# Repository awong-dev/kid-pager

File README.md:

# Low-powered Kid Pager

## What is this and why does it exist?
Using expensive smart watches with also expensive cellular plans just so kids
can message their parents is ridiculous. The idea is to get something that
can run for a few dollars a month, be rugged in a backpack, and not require
constant changing.

Enter the Kid Pager.

This project builds a simple, customizable, location enabled, pager-style
device and accompanying Relay Server that can be fitted with an
ultra-cheapo SIM card to provide a mobile communication and location
system for coordinating with a child.

The Relay Server is designed to run on free-tier cloud services or on a
home server.  The complexity of the server is a bit above running a
Plex server.

The hardware is designed to be buildable by DIY hobbyists who know how
to do basic soldering.

Using the current bill of materials and the provided Relay Server, the
current prototype fits inside an Altoids Tin and has the following basic
features:
   * $2-$3/month for a soracom global coverage sim that talks to custom
     Chat server.
   * 2 week battery life per charge for basic usage
   * 2.9" e-ink screen so there NO blue light
   * _sluggish_ UI response (think kindle) to increase threshold for usage
   * GPS/GNSS and cell-tower location
   * full QWERTY keyboard
   * Temperature monitor cause everyone needs hour read of their kid's
     backpack temperature.

Because it is text only, the data usage is tiny so the data-only Soracom
sim never goes much above the base rate of $2.

We've been using this our family for about 2 months now with the thing being
beaten around inside a kid's backpack.

## Basic functionality and how it works

### Kidpager Relay Server + Native Chat
The system relies on a web-technology Relay Server for handling chat messages,
keeping location data, doing device management, pushing firmware updates, etc.
The Relay Server is the centrol point of control with all messages passing
through it so the parent can allow/deny/audit communications as makes
sense for their family.

It exports a web interface that can be used for sending/receiving chats
as well as for device management. This means your child can log into the
webpage at the home computer if they want instead of using the device
hardware allowing for access to a full keyboard when at home.

For the parent, the webpage is a "Progressive WebApp" and can be "installed"
on to your phone so that you can receive push notifications for new messages
from the native chat system.  This is actually not required for usage if
SMS or bridges into other chat systems are used (see later sections).

The Relay Server is is designed to run on the free tier of Google Firebase.
There is also a docker version so you can have complete control of the data.

### Talking to other families (Federation)

There is also federation support so that two families with different Relay
servers can register one-another to send messages back and forth.

It is also possible to host multiple families on one Relay Server. Which
one makes sense depends on data privacy considerations as to who may
access location + chat history for each family. In a multi-tenancy setup,
the admin has access to multiple families worth of data, but one admin
could host the setup for many people.

In a federated approach, only the authorized chat messages that cross the
boundries are forwarded but each family would have to run their own server.

### Extension #1: SMS
As a child gains more independence, being able to send messages to
others with SMS allows them the independence to extend their messaging
network.

Also, in emergency situations, it is frustrating to have a cellular
device, but not be able to reach someone even if you have their phone number.

Enabling SMS can be done by replacing the data-only Soracom sim with one
that supports SMS as well.

The SMS capabable SIM can be used two way:
  1. Installed directly on the device in place of the Soracom Sim.
  2. Installed in an android phone that you remote control (see Android Bridge section)

For (1), the SIM will also need a small data plan. For (2), it can be
an SMS only plan.

In either configuration, because it is a child device, all SMS
communication is controlled the Relay Server. Even in configuraiton
#1, though the device technically receives the SMS directly, the firmware
actually just passes it back up to the Relay Server so policies can be
applied. Only if it is deemed okay is it passed back to the child. This way
no random SPAM SMS messages can come through and the Relay Server always
maintains control over what the device can do.

### Extension #2: Android Bridge for SMS/WhatsApp/Google Chat/etc
This is a total hack that will likely be flaky but has worked
pretty well so far.

For this, you:
  1. Get an old android phone and leave it permanently plugged in
  at home.
  2. Install a SMS-only SIM card into that phone. (Now you have
  two SIM cards -- the $2/month Soracom in the Kid Pager device and
  a cheapo $5/month SMS-only one in the Android)
  3. Connect the phone to your wifi network to remove the need for data.
  4. Install whatever chat-apps you want and log them in.
  5. Side-load the custom Android Bridge app here that allows the Chat
  Server to remote control the Android phone.

The Android Bridge app works effectively as a remote-control for
the phone. When the pager wants to do an SMS or talk to WhatsApp
or Google chat, it sends a message to the Relay Server which then
directs the phone to forward it onwards. Incoming messages follow
that path in reverse.

Adding a new app can be done by direct Claude to vibe code an
interface.

Note that bridge does NOT give the pager device access to an entire
chat app (eg all WhatsApp contacts). Rather it subscribes to individual
conversations Relay Server. This is clunky but in a way better because
you have more fine grained control.

Why go through this complexity? Because ultimately, a custom closed
Relay Server, even with SMS, is too restrictive for the modern
communication envrionment.

However, any such bridge is fragile relying on hacks to watch
notifications, drive the UI via accessibility featuers, etc. It will likely
have bugs as time goes on.

## Hardware
The provided design uses an Altoids tin cause it looked cool. It's actually
not that great since it being metal which requires a much more expensive
external antenna that might be broken.

### Making it smaller.
The full QWERTY keyboard largest problem with shrinking the size
of the device.  After that, it's the antenna.  The battery can be
shrunk to whatever you want with a tradeoff of time-between charges.
(With a 2500 mAh battery, the system lasts about 2 weeks a charge)

So the first thing to play with is using a T-9 input system, a plastic
case so you can use a flex antenna on the inside of the case, and then
a smaller screen. You could probaby get close to an old Nokia style
candybar phone.

This would also have the benefit of possibly shaving up to $20/device off
the hardware cost as the external antennas are that much more expensive
that the internal ones.

## Privacy and Parental controls.

### Who can contact your kid + see their location
The Relay Server was designed with permission model close to a network firewall.

For each contact you can decide if

  1. Pager can send to contact
  2. Pager can receive from contact
  3. Contact may view or request location of Pager

For new and unknown contacts you can also set a policy to default allow or deny
any of the above.

A sensible configuraiton, for example, could be:
  1. Allow all send/receive from entries in a parent controlled Address Book
  2. For unknown contacts on SMS, allow if pager initiates, but log and notify the parent. This allows a kid to help a friend talk to the friend's parent.
  3. Disallow all inbound SMS to the pager number from an unknown contact, but log and notify parent. Prevents spam and also some protection against cyberbullying/harassment.

Of you could lock it down so that no one can communicate at all without the parent creating an explicit allow list,

## FAQ

### What happens with pictures and videos?

This thing is text only. The chat server will send a note that an [image] pr [video] was sent but that's it.

### What about other langauges?
The pager is built around unicode and is i18n ready! I even asked Claude to leave some hooks for an
IME (which could also be used for T-9 and predictive typing).  The problem with languages is fonts
and how much space to use in the font.  Currently, I have it doing a large chunk of Chinese and some
emojis. But you can swap that out.  The font is stored in a different partition from the code
and can be updated from the web.

### How do you update the firmware?
The Relay Server is able to push updates down for an Over The Air update (OTA) using the ESP32's OTA
infrastructure.  This allows pushing fonts also.  Firmware pushes use delta encoding making them
often around 50kb to 70kb in size which works prefectly fine in a 100Mb/month data plan.

### How does the protocol work?

In a nutshell, a provisioend Pager device maintains a connection to an MQTT
broker which provides a bidirectional channel to and from the Relay Server's
REST APIs. Provisining bind a pager to a broker and provides certs to
authenticate, sign, and/or encrypt messages as needed.

This channel is used to sent chat messages, location, and status updates. Data
is encoded in signed CBOR blob.

MQTT is used instead a direct TCP connection because it allows the Pager moden
to make heavy use of of eDRX power saving mode on LTE-M where it can sleep
while still staying on the network.

On a non-Soracomm sim, this connection is done with MQTTS using the provisioned
certs. This ensures an encrypted transmission across the open internet back to
the Relay Server, but incurs a fairly high TLS overhead for sending really short
messages.

With a Soracom SIM, Soracom Beam is used to avoid this. Instead of doing TLS
ourselves, plain MQTT is used to the Soracom Beam server. For this first hop,
we rely on the LTE layer to provide encryption which vastly reduces data usage
from the Pager on the cell plan. Soracom's Beam's proxy then creates a MQTTS
connection to our broker for transiting the open internet. Soracom's security
model guarnatees a secure network between the LTE termination and their
Beam endpoint so the threat model basically reduces to nation state that has
broken into a teleco system. That point which seems a good trade for saving
a lot of encryption handshake overhead (data usage + battery usage).

The Relay Server itself is just standard web techs (https, etc).

### How does location tracking work?

Location is derived from both cell-tower triangulation as well taking an
optional GNSS (superset of GPS) "fix" on the current location and broadcast
to the server.  The frequency of updates depends on whether the device is
in motion.  The device has an accelerometer which, when activated, causes
a faster location send. Otherwise, if it's just sitting in a backpack
for an hour, energy isn't wasted on updating location.

By nature of being on a cellular network, this is always some location
data avaliable for free just by nature of talking to a cellular antenna.
Within this part of Seattle, the precisions is frequently as good as
GNSS while also working inside buildings (that have cell signal) and
also being many times more power efficient.

However, if wanted, a GNSS antenna can be fitted on the device so it
can do a real GPS fix when there is line-of-sight to the sky.

### Can location be requested?

Yup. The Relay Server can send a signal down to tell the firmware that
location has been requested.

### Can I introduce filters on messages?

This thing is fairly simple web app that was almost entirely built with Claude
so by default there's no such functionality.

But because it is so simple, if you wanted to modify it so that messages
pass through some filter to do someething (eg, search for the word "applejack"
so that you can send an emergency broadcast to the City Spies), it'd be
very easy.

Or if you want to get super fancy, you could imagine sending everything into
an LLM that tries to do some sort of advanced cyberbullying detection...or
even process a code-switched multi-lingual chat to always provide some
sort of base translation.

Honestly, the sky's the limit.

But, personally, I think the expected use case is meant for "r u here yet?"
messages where the response is stuff like "almost. 5m."

## Technical details

### Repository layout

| Path | What it is |
|---|---|
| `docs/` | Design documents. Start at `docs/README.md`. `PROTOCOL.md` is the authoritative wire contract that code conforms to. |
| `firmware/` | ESP-IDF firmware for the Walter (ESP32-S3 + Sequans GM02SP) device. See `firmware/README.md` for build and bench steps. |
| `relay/` | FastAPI relay: webhook ingest, routing, delivery backends, admin and conversation APIs, device provisioning, authentication, retention. See `relay/README.md` to run it locally. |
| `web/` | Next.js + MUI web app on Firebase (Auth, Firestore listeners, FCM). See `web/README.md`. |
| `bridge-android/` | Android app that relays a member's SMS, voice and chat conversations to the relay (the bridge phone). |
| `home/` | Docker Compose stack for running the whole service on one machine you own. `setup.sh` writes its configuration. See `home/README.md`. |
| `hardware/` | Carrier board and enclosure design files. |
| `infra/` | Terraform for GCP (Cloud Run, Firestore, Firebase Hosting and Auth, Scheduler, Tasks, Secret Manager, Workload Identity Federation). See `infra/README.md`. |
| `tools/` | `pager_client.py` (simulated device and server driver), `e2e_v2.py` (end-to-end suite against the local stack), `send.py`, `provision.py`, `emqx_setup.py`. |
| `.github/workflows/` | `ci.yml` runs the relay unit tests and the end-to-end suite on push. `deploy.yml` builds the relay image and applies Terraform on a push to `main`. |

## Running your own server

The whole service runs on one machine you own, such as a Raspberry Pi, a NAS or a mini PC, with
Docker. You need a name that points at your home (a dynamic-DNS name is fine), a router that can
forward ports to that machine, and a reverse proxy (nginx or traefik) that already serves https
for that name.

```bash
cd home
./setup.sh               # asks for your server's name, writes the configuration, prints what to add to your proxy
docker compose up -d     # builds and starts the relay and the broker
```

`setup.sh` prints the nginx or traefik configuration, the ports to forward on your router and the
address to open to create the first admin. [`home/README.md`](home/README.md) is the full runbook:
ports, certificates, running without a proxy of your own, backups, automatic security updates and
Soracom Beam.

## Running a development stack

This is for working on the code, not for real use. Run the local stack (broker, Firebase emulators
and relay) and the end-to-end suite:

```bash
# Start the local stack (EMQX, Firebase emulators, relay)
cd relay
docker compose up -d --build
cd ..
python3 tools/emqx_setup.py
```

```bash
# [optional] Run all test scenarios, in text and CBOR wire encodings
relay/.venv/bin/python tools/e2e_v2.py
relay/.venv/bin/python tools/e2e_v2.py --wire cbor

# Or run individual scenarios
relay/.venv/bin/python tools/e2e_v2.py bootstrap setup_code address_book
```

Scenarios: `bootstrap`, `text_roundtrip`, `allowlist`, `republish`, `location_periodic`,
`location_on_demand`, `retention`, `bytes`, `address_book`, `setup_code`, `sms_log`, `bridge`,
`bridge_voice`, `bridge_whatsapp`, `receipts`, `bridge_health`. The implementation is in
`tools/e2e_v2.py`.

Unit tests and manual checklists are documented in `relay/README.md`, `web/README.md` and
`firmware/README.md`.

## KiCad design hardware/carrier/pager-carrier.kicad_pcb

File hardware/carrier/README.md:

# pager-carrier and pager-panel

KiCad 10 projects for the carrier board that replaces the Adafruit breakouts
around the Walter module, and for the small panel board that drives the
2.9" SSD1680 e-ink glass. The panel board sits between the glass and the
battery and is cabled to the carrier over a JST SH cable.

**Carrier: hand-edited.** The carrier `.kicad_sch` files are the source of
truth; `gen/carrier.py` / `gen/carrier_pcb.py` / `gen/build.py` describe an
earlier generated revision and must NOT be re-run (they overwrite the hand
edits). The sections below describe that generated revision; reference
designators and some parts differ in the hand-edited schematic.

**Panel: generated.** `gen/panel.py` + `gen/panel_pcb.py`; regenerate only the
panel with a driver that calls `build.build_panel(True)` (never `build.py`'s
main, which rebuilds the carrier too), then `panel_pcb.py --route` and
`finish_pcb.py panel` with KiCad's python.

## Layout of this directory

| Path | What |
|---|---|
| `pager-carrier.kicad_pro/.kicad_sch/.kicad_pcb` | carrier project, root schematic, board |
| `power.kicad_sch` … `peripherals.kicad_sch` | the five hierarchical sheets |
| `pager-carrier.kicad_sym`, `pager-carrier.pretty/` | project symbols (Walter, BQ25185, TPS62840, LIS2DW12, DRV2605L, MAX17048, rail power symbols) and custom footprints (Walter, BQ25185, TPS62840, USB4235, FH34SRJ 24S/6S) |
| `panel/` | pager-panel project (display ZIF, front-light ZIF, boost, 10-way SH), shares the symbol library above |
| `out/`, `panel/out/` | ERC and DRC reports, schematic PDF, BOM CSV, netlist, Freerouting DSN/SES |
| `gen/` | generator: `build.py` (schematics + exports), `carrier_pcb.py` / `panel_pcb.py` (boards, run with KiCad's python), `finish_pcb.py` |

The board scripts run under KiCad's python
(`/Applications/KiCad/KiCad.app/Contents/Frameworks/Python.framework/Versions/Current/bin/python3 gen/panel_pcb.py --route`).
`--route` needs a Freerouting jar: set `FREEROUTING_JAR`, or put it at
`gen/freerouting/freerouting-2.5.0.jar`.

## Custom footprints and where their numbers came from

- `Walter_Module_2x14_THT`: datasheet rev 1.1 (hw 1.6) section 6 plus the
  vendor `walter-solder.kicad_mod`. Rows 17.78 mm
  apart, 2.54 pitch, pin 1 at 9.72 mm from the USB-C end, 1.02 drill / 1.7 pad.
  The carrier sits above a header-side-up Walter, so the pattern is the
  **mirror** of the vendor's: pin 1 is on the +X row as seen from the carrier
  top. SIM holder, u.FL jacks and USB-C are marked on User.Comments.
- `BQ25185_WSON-10_DLH0010A_2.2x2mm_P0.4mm_EP0.9x1.5mm`: TI drawing 4226298/A
  (datasheet SLUSF65B): pads 0.5 x 0.2 on 0.4 pitch, columns 2.1 mm apart,
  thermal pad 0.9 x 1.5 with two 0.2 mm vias. Matches the SnapEDA footprint
  and KiCad's stock
  `Texas_DLH0010A_WSON-10-1EP_2.2x2mm_P0.4mm_EP0.9x1.5mm` pad for pad.
- `USB_C_Receptacle_GCT_USB4235_Vertical`: GCT drawing rev A.
  16 pads 0.30 x 0.87 on 0.5 pitch at x = ±0.25/0.75/1.25/2.75, rows at
  y = ±0.87; plated shell slots 0.6 x 0.85 (1.1 x 1.35 copper) at x = ±5.0; NPTH
  pegs 0.6 mm at x = ±3.75. Height 6.5 mm. Only ordering code: USB4235-03-C.
- `TPS62840_VSON-HR-8_DLC0008B_1.5x2mm_P0.5mm`: TI DLC0008B land pattern, pads
  0.6 x 0.25 at x = ±0.65 (the stock SOT-583-8 is 0.09 mm wider per side).
- `Hirose_FH34SRJ-24S-0.5SH` and `-6S-`: Hirose FH34SRJ catalog
  page 4 land pattern: contact pads 0.3 x 0.8 on 0.5 pitch, fitting pads
  0.4 x 0.8 at the E/F spans 3.3 mm behind the contacts; body D wide, 3.8 deep,
  **1.0 mm high**, top and bottom contact, back-flip actuator. Pin 1 at -X with
  the contacts (FPC entry) at -Y, the same convention as KiCad's FH12 footprints.
  KiCad 10 ships no FH34SRJ footprints.

## Mechanical placement (carrier, 85 x 52 mm, 1.0 mm FR4)

- Walter crosswise under the left 26 mm (its 55 mm axis runs across the 52 mm
  board width); header centre at (13.5, 24.73). USB-C end of the Walter at the
  top edge, antenna/SIM end at the bottom edge.
- Antenna notch 12 x 6 mm at the top-left edge (x 2.5–14.5): the u.FL jacks are
  at the Walter's **USB-C end**, not the antenna end.
  3 mm all-layer keep-outs around both jacks.
- Top strip (y 0–8): vertical USB-C J1, slide switch SW1, 10-way panel cable
  J3, battery J2 (cables exit toward the tin wall).
- Glass region (y 8–44.7, x 0.5–79.5): parts ≤ 2 mm only. Right end
  (x 62–79.5) left empty for the panel board.
- Bottom strip (y 44.7–52): keyboard J4 (cable up to the CardKB in the lid),
  LED J6 and haptic J7 (DNP), the 14 test pads (1.5 mm pitch), and the
  front-light button SW2 at the right end (80, 48.4), marked LIGHT.
- Walter region, top side only, between the header rows: CP2102N cluster,
  SN74LVC2G126 + UMH3N auto-reset, BQ25185 cluster, P-FET switch parts.
- Mounting holes H1–H4 at (17, 2.5), (82.8, 2.2), (82.8, 43.5), (2.5, 49.5).

## Part heights (low profile is critical; the CardKB lives in the lid)

| Part | Height above its board |
|---|---|
| J1 USB4235 vertical USB-C | 6.5 mm (the horizontal fallback is 3.2) |
| J2, J4 JST PH side-entry (S2B/S4B-PH-SM4-TB) | 5.5 mm (6.0 deep; JST ePH catalog p.4) |
| SW1 slide switch JS102011SAQN | 3.5 mm |
| J3 JST SH side-entry SM10B-SRSS-TB | 2.9 mm |
| SW2 tactile SKQGAFE010 | 1.5 mm (sits beside the glass, below the glass top) |
| everything under the glass | ≤ 1.3 mm: 0805 caps 1.25, SOT-23 1.1, QFN 0.9, L2 1.0 |
| glass GDEY029T94-FL03 | 2.01 mm incl. the front-light plate |
| panel board | 1.0 mm FR4 + 1.5 mm (L1) ; FH34SRJ ZIFs 1.0, SOD-123 1.1 — a 0.8 mm board is fine |

So above the carrier: glass stack ≈ 1.3 + 2.0 (or panel 1.0 + 1.5 + 2.0 at the
tail end), and the USB-C at 6.5 is the only thing taller than 3.5 mm.

## Design notes

1. **CP2102N package**: the GQFN20 has no DTR pin, so auto-reset is
   impossible with it. U5 is **CP2102N-A02-GQFN24** (DTR pin 23, RTS 19,
   VIO tied to VDD, RSTb pull-up 1 k per datasheet, VBUS sense via
   22.1 k / 47.5 k, 4.7 µF + 100 nF per supply pin).
2. **TPS62840DLCR is not a fixed 3.3 V part**: VSET takes a 267 k resistor to
   GND for 3.3 V; pin 8 is VOS (output sense), wired to 3V3.
3. **PWR_FLAG**: SYS is driven by the charger's SYS power-output pin, so a
   flag there is an ERC error and SYS has none; the other rails keep theirs.
4. **TPS22917 QOD** left open (open-collector to power-output is an ERC
   error); tie to VOUT in layout if quick discharge of the panel rail is wanted.
5. **Panel reference circuit** follows the GDEY029T94 spec sheet:
   RESE 2.2 Ω, L1 47 µH ≥ 0.43 A (cjiang
   FNR3015S470MT, 3 x 3 x 1.5 mm), 1 MΩ GDR pull-down, FPC pin 5 = VSH2 and
   pin 20 = VSH1 (both 1 µF/25 V), VPP open. Diode orientation: D2 anode on
   the pump node, D1 anode on VGL.
6. **ISET** is 604 Ω (600 Ω is not an E96 value): 497 mA. ILIM/VSET 18 k gives
   the 500 mA limit (475 mA typ) with 4.20 V; the DNP alternate is 13 k
   (1.1 A), not 1 A.
7. **TS/MR**: a single 10 k to GND, per the datasheet "TS not used" text.
8. **Front light = GDEY029T94-FL03**: the light has its own
   6-pin 0.5 mm flex (pins 1-2 anode, 3-4 NC, 5-6 cathode; 4 LEDs in parallel,
   Vf 2.75/2.8/3.3 V, 60 mA max; 3.5 mm wide, ~30 mm long, leaves the glass at
   the corner next to the display tail). Its ZIF (panel J3, FH34SRJ-6S) is on
   the panel board and the anode/cathode ride the panel cable (pins 9/10), so
   the cable is a 10-way SH. The ballast is 0 Ω and Q4 (AO3400A) carries a
   15 Ω source resistor with an MMBT3904 base-emitter across it, a ~45 mA
   clamp that is independent of SYS and of firmware; the 1 k gate resistor
   lets the BJT pull the gate down. Dim with FL_PWM. Fits both the FL03
   (60 mA max) and the Orient AEZ122250A00 light (3 LEDs, 45 mA at Vf 3.3 V).
8b. **Two front-light ZIF positions on the panel board.** The 6-pin
   light flex pinout (1-2 anode, 3-4 NC, 5-6 cathode) is the same on both
   panels, but where the tail leaves the glass is not. J3 "FL-A" (fitted)
   is for the FL03 tail; J4 "FL-B" (DNP) is for the Orient
   AEZ122250A00-2.13ENRWS tail. The Orient light's pin numbers run opposite
   to its display tail's, so J4 is wired 1-2 cathode / 5-6 anode. The cable's
   FL_P / FL_N reach FL_A / FL_K through two bridged solder jumpers JP1/JP2
   (1-2 bridged = straight; cut and bridge 2-3 = crossover), so a tail whose
   polarity turns out mirrored is a jumper change. The display ZIF J1 and its
   reference circuit (47 µH, 2.2 Ω, MBR0530, 1 µF/25 V, BS1 low) are
   identical in the Good Display and Orient sheets, so the same panel board
   takes either glass.
   From the drawings (GDEY029T94-FL03-CAD.pdf and AEZ122250A00-2.13ENRWS
   rev 1.0 p.5): both front-light tails leave on the **pin-24 side** of the
   display tail (front view). FL03: tail centre 15.5 mm from the display tail
   centre (display tail left edge 10.42 from the LGP edge + 0.80 LGP inset,
   12.50 wide; FL tail 3.50 wide, 2.00 from the glass corner), 11.5 mm long
   with the contacts at 9.5-11.5, so J3 sits in the edge row. Orient 2.13":
   10.8 mm, FL tail 20.0 mm long (contacts 17.8-20.0), display tail 14.3 mm;
   its FL pins run 6->1 away from the display tail. Both ZIFs therefore sit
   left of J1 on the board (J1 pad 24 is on the left): J3 at J1.x-15.5 in the
   edge row, J4 at J1.x-10.8 one row inboard, since 5.5 mm wide ZIFs 4.7 mm
   apart cannot share a row.
9. **Front-light button** SW2: FL_BTN on IO4 (header pin 15,
   RTC GPIO so it can be an ext1 wake), 100 k pull-up to 3V3, 100 nF, switch to
   GND. TP13 is on the same net.
10. **Fuel gauge** U10 is populated. CELL and VDD both on VBAT,
    QSTRT and CTG to GND, EP to GND.
11. **MAX17048 footprint**: stock `TDFN-8-1EP_2x2mm_P0.5mm_EP0.8x1.2mm`
    (matches the Maxim 21-0168 drawing); DRV2605L uses `TSSOP-10_3x3mm_P0.5mm`
    (TI DGS land within 0.05 mm).
12. **Walter mounting**: the datasheet has no header-side-up guidance; the
    nano-SIM then faces the carrier and loads from the antenna end, which is
    within ~1 mm of the tin wall. Fit the SIM before mounting.
13. **References**: Q2 is one UMH3N holding both auto-reset transistors; the
    carrier's 10-way display connector is J3; the panel board
    owns the display ZIF (J1), L1, Q5, D1–D3, R4, C3–C5, plus the
    front-light ZIF as J3.
14. **BOM**: SN74LVC2G126DCUR (VSSOP-8) and USB4235 are not stocked by
    LCSC/JLCPCB (hand-place; DCTR is MSOP-8 0.65 mm, a different footprint).
    The BOM carries LCSC numbers; basic parts preferred.
15. **Routing** is Freerouting's output (GND routed as tracks, then pours on
    both layers). The boost loop on the panel and the USB D+/D− pair deserve
    a manual look.

## Sleep-current audit

Battery only, SW1 on, Walter asleep. Carrier parts, from the datasheets:

| Consumer | Sleep current | Note |
|---|---|---|
| BQ25185 battery quiescent (IQ_BAT) | 4 µA typ, 5 max | unavoidable while the cell is connected |
| MAX17048 | 3 µA hibernate (23 µA active) | firmware must leave HIBRT at its default so it auto-hibernates, or force hibernate |
| TPS62840 3V3 buck | ~0.1 µA (36 nA VIN + 56 nA VOS) | |
| TPS22917 (3V3_EPD off) | 10 nA | 0.5 µA when on |
| LIS2DW12 low-power mode 1 | ~1 µA | shake wake; 50 nA if powered down |
| Q1 gate network | **1.9 µA** | 2.2 M pull-up (a 100 k would draw 38 µA); the ON switch pulls the gate low through 10 k + pull-up |
| SN74LVC2G126 U6 | **0** | VCC is BRG_VDD (CP2102N regulator), so it is unpowered without USB; Ioff outputs, ESP_RX0 held by its 10 k |
| CP2102N | 0 | bus powered |
| STAT/ACC/RX0/FL_BTN pull-ups, VBUS dividers | 0 | all idle high or on VBUS |
| front light, Q4, keyboard rail, panel rail | 0 | switched off |

Carrier total ≈ 10 µA on top of the Walter's own deep-sleep draw. The fuel
gauge is the biggest remaining item.

## TPS62840 fixed-voltage question

There is no fixed-3.3 V part. Every TPS6284x orderable (TPS62840 1.8–3.3 V,
TPS62841 0.8–1.55 V, TPS62842 1.8–3.6 V; DLC, YBG and DGR packages) sets its
output with the VSET resistor. The 267 k 0603 stays.

## Open questions

- Tin interior height with the lid closed versus 8.5 + 1 + 6.5 (USB4235) mm.
- GDEY029T94 tail pin-1 side after the 180° fold. The FH34SRJ has contacts
  on both faces, so the fold cannot leave the tail unconnected, but a wrong
  face mirrors the pin order (1↔24). The footprint uses the FH12
  bottom-contact convention; confirm on a physical panel
  before ordering. Same for the 6-pin front-light tail (a mirror there only
  swaps anode and cathode: no light, no damage; fix = change JP1/JP2 on the
  panel board).
- UC8151 / IL0373 panels (Good Display GDEW series, Waveshare non-V2) use a
  different RESE value; if those must fit, give R4 a second parallel 0603
  footprint and confirm the value from a specific sheet.
- Walter header geometry against a physical module before ordering.
- Battery lead polarity (Adafruit 328) versus J2 pin 1.
- LTE peak current at VIN, to confirm 100 µF + 10 µF and the
  P-FET drop at a 3.4 V cell.
- Where exactly the panel board sits relative to the glass tail (the carrier
  keeps x 62–79.5 under the glass clear for it).

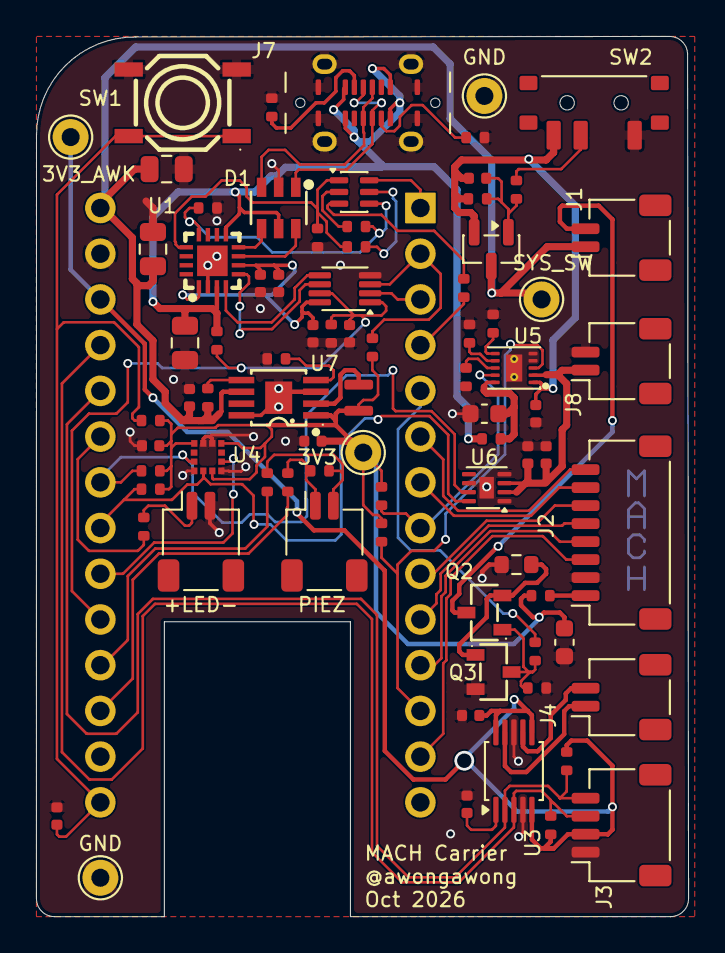
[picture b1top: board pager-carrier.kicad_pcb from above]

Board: 2 copper layers, 36.2 x 48.9 mm, 81 parts (0 on the bottom side), 63 nets.

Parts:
C1: 10uF; C_0805_2012Metric
C2, C4, C8, C11, C13, C16, C17: 100nF; C_0402_1005Metric_NoSilk
C3, C9, C10: 1uF; C_0402_1005Metric_NoSilk
C5, C6: 22uF; C_0805_2012Metric
C7: 10uF; C_0603_1608Metric
C12: 1uF; C_0603_1608Metric
C14, C15, C18, C19: 10uF; C_0402_1005Metric_NoSilk
D1: USBLC6-2SC6_C2687116; SOT-23-6_L2.9-W1.6-P0.95-LS2.8-BL
J1, J4, J5, J6, J8: Conn_01x02; JST_SH_SM02B-SRSS-TB_1x02-1MP_P1.00mm_Horizontal
J2: Conn_01x08; JST_SH_SM08B-SRSS-TB_1x08-1MP_P1.00mm_Horizontal
J3: Conn_01x04; JST_SH_SM04B-SRSS-TB_1x04-1MP_P1.00mm_Horizontal
J7: USB_C_Receptacle_USB2.0_16P; USB_C_Receptacle_ShouHan_TYPE-C-16PLT-H6.5_Vertical
L1: 2.2uH; L_Murata_DFE201610P_NoSilk
M1: Walter; Walter_Module_2x14_THT
Q1: UMH3N; SOT-363_SC-70-6
Q2: AO3400A; SOT-23-3_L2.9-W1.3-P1.90-LS2.4-BR
Q3: MMBT3904-C20526; SOT-23-3_L2.9-W1.3-P1.90-LS2.4-BR
Q4: AO3401A; SOT-23
R1, R2, R3, R9, R31, R32: 100k; R_0402_1005Metric_NoSilk
R4, R5, R11, R21, R23, R25, R27: 10k; R_0402_1005Metric_NoSilk
R6, R7, R20: 0R; R_0402_1005Metric_NoSilk
R8: 1k; R_0402_1005Metric_NoSilk
R10: 15R; R_0603_1608Metric
R12, R13, R14, R15, R26, R28: 4.7k; R_0402_1005Metric_NoSilk
R16, R17, R18: 220R; R_0402_1005Metric_NoSilk
R19, R29: 1M; R_0402_1005Metric_NoSilk
R22: 18k; R_0402_1005Metric_NoSilk
R24: 620R; R_0402_1005Metric_NoSilk
R30, R33: 51k; R_0402_1005Metric_NoSilk
SW1: TS-1187A-S16; SW-SMD_4P-L5.2-W5.2-P3.70-LS6.4
SW2: SW_SPDT; SW_SPDT_ShouHan_MSS12C02LS_TopActuated
TP1: 3V3; TestPoint_THTPad_D2.0mm_Drill1.0mm
TP2: SYS_SW; TestPoint_THTPad_D2.0mm_Drill1.0mm
TP3, TP5: GND; TestPoint_THTPad_D2.0mm_Drill1.0mm
TP4: 3V3_AWK; TestPoint_THTPad_D2.0mm_Drill1.0mm
U1: CH343P; TQFN-16_L3.0-W3.0-P0.50-BL-EP1.7
U2: 74LVC2G126; VSSOP-8_2.3x2mm_P0.5mm
U3: DRV2605LDGSR; TSSOP-10_3x3mm_P0.5mm
U4: LIS2DW12TR-MS; LGA-12_2x2mm_P0.5mm_NoSilk
U5: BQ25185DLHR; BQ25185_WSON-10_DLH0010A_2.2x2mm_P0.4mm_EP0.9x1.5mm
U6: MAX17048G+T10; TDFN-8-1EP_2x2mm_P0.5mm_EP0.8x1.2mm
U7: TPS62842DGRR; HVSSOP-8_L3.0-W3.0-P0.65-LS4.9-BL-EP

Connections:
3V3: C7.1, C11.1, C19.1, L1.2, R3.2, R7.1, R11.2, R14.1, R15.1, R23.1, R25.1, TP1.1 (1_1), U4.3 (VDDIO), U4.7 (VDD), U4.10 (CS), U7.1 (VOS)
3V3_AWK: C9.1, J3.2, M1.26 (3V3_OUT), R12.1, R13.1, TP4.1 (1_1), U3.5 (EN), U3.6 (VDD/NC), U3.10 (VDD)
/Core/3V3_J1: J2.1, R7.2
/Core/ACC_INT1: M1.20 (IO16), U4.5 (INT1)
/Core/AWK_EN_N: M1.4 (DFU/3V3_EN), R6.2
/Core/AWK_SCL: J3.4, M1.24 (IO9), R13.2, U3.2 (SCL)
/Core/AWK_SDA: J3.3, M1.25 (IO10), R12.2, U3.3 (SDA)
/Core/BRG_3V3: C2.2, C3.2, C8.1, U1.1 (VIO), U1.6 (V3), U2.8 (VCC)
/Core/BRG_RXD: U1.5 (RXD), U2.6
/Core/BRG_TXD: U1.4 (TXD), U2.5
/Core/EINK_BUSY: J2.8, M1.6 (IO11)
/Core/EINK_CS: J2.5, M1.10 (IO40)
/Core/EINK_DC: J2.6, M1.9 (IO39)
/Core/EINK_MOSI: J2.4, M1.11 (IO41)
/Core/EINK_RST: J2.7, M1.7 (IO13)
/Core/EINK_SCK: J2.3, M1.13 (IO2)
/Core/ESP_EN: M1.1 (RESET), Q1.6 (C1)
/Core/ESP_RX0: M1.2 (IO44/RX0), R11.1, U2.3
/Core/ESP_TX0: M1.3 (IO43/TX0), U2.2
/Core/EXT_LED: M1.23 (IO8), R18.1
/Core/FL_BTN: C4.1, M1.15 (IO4), R3.1, SW1.1, SW1.2
/Core/FL_N: J1.2, Q2.3 (D)
/Core/FL_PWM: M1.5 (IO12), R8.1
/Core/PIEZ_N: M1.18 (IO7), R17.1
/Core/PIEZ_P: M1.17 (IO6), R16.1
/Power/SW: L1.1, U7.2 (SW)
/Power/SYS: C13.2, C14.1, Q4.2 (S), R29.2, SW2.3 (C), U5.1 (SYS)
/Power/SYS_GATE: C13.1, Q4.1 (G), R27.2, R29.1
/Power/VBAT: C15.1, C16.1, J8.1, U5.2 (BAT), U6.2 (CELL), U6.3 (VDD)
/Power/VSET: R33.1, U7.4 (VSET)
AON_SCL: M1.22 (IO18), R15.2, U4.12 (SCL), U6.7 (SCL)
AON_SDA: M1.21 (IO17), R14.2, U4.2 (SDA), U6.8 (SDA)
CHG_STAT1: M1.8 (IO38), R23.2, U5.9 (STAT1)
CHG_STAT2: M1.12 (IO42), R25.2, U5.3 (STAT2)
GND: C1.2, C2.1, C3.1, C4.2, C5.2, C6.2, C7.2, C8.2, C9.2, C10.2, C11.2, C12.2, C14.2, C15.2, C16.2, C17.2, C18.2, C19.2, D1.2 (GND), J2.2, J3.1, J5.2, J7.A1 (GND), J7.A12 (GND), J7.B1 (GND), J7.B12 (GND), J7.SH (SHIELD), J8.2, M1.27 (GND), Q3.2 (E), R1.2, R2.2, R9.2, R10.2, R21.2, R22.2, R24.2, R26.2, R28.2, R31.2, R33.2, SW1.3, SW1.4, SW2.1 (A), TP3.1 (1_1), TP5.1 (1_1), U1.2 (GND), U1.17 (EP), U2.4 (GND), U3.4 (IN/TRIG), U3.8 (GND), U4.1 (SDO/SA0), U4.4 (NC(GND)), U4.8 (GNDIO), U4.9 (GND), U5.4 (~CE), U5.5 (GND), U5.11 (EP), U6.1 (CTG), U6.4 (GND), U6.6 (QSTRT), U6.9 (EP), U7.3 (MODE), U7.8 (GND), U7.9 (EP)
unnamed: D1.1 (I/O1), J7.A6 (D+), J7.B6 (D+)
unnamed: D1.3 (I/O2), J7.A7 (D-), J7.B7 (D-)
unnamed: J4.1, U3.9 (OUT-)
unnamed: J4.2, U3.7 (OUT+)
unnamed: J5.1, R18.2
unnamed: J6.1, R16.2, R19.2
unnamed: J6.2, R17.2, R19.1
unnamed: J7.A5 (CC1), R28.1
unnamed: J7.B5 (CC2), R26.1
unnamed: Q1.2 (B1), R4.2
unnamed: Q1.1 (E1), R2.1, R5.1, U1.13 (RTS)
unnamed: Q1.5 (B2), R5.2
unnamed: Q1.3 (C2), R6.1
unnamed: Q1.4 (E2), R1.1, R4.1, U1.12 (DTRTNOW)
unnamed: Q2.1 (G), Q3.3 (C), R8.2, R9.1
unnamed: Q2.2 (S), Q3.1 (B), R10.1
unnamed: R27.1, SW2.2 (B)
unnamed: C10.1, U3.1 (REG)
unnamed: R22.1, U5.7 (ILIM/VSET)
unnamed: C12.1, R20.2, U5.10 (IN)
unnamed: R24.1, U5.8 (ISET)
unnamed: R21.1, U5.6 (TS/MR)
unnamed: R32.2, U7.5 (EN)
SYS_SW: C5.1, C6.1, C18.1, J1.1, M1.28 (VIN), Q4.3 (D), R32.1, TP2.1 (1_1), U7.6 (VIN)
USB_DM: D1.4 (I/O2), U1.8 (UD-)
USB_DP: D1.6 (I/O1), U1.7 (UD+)
VBUS: C1.1, D1.5 (VBUS), J7.A4 (VBUS), J7.A9 (VBUS), J7.B4 (VBUS), J7.B9 (VBUS), R20.1, R30.1, U1.3 (VDD5), U1.9 (VBUS)
VBUS_DET: C17.1, M1.19 (IO15), R30.2, R31.1, U2.1, U2.7

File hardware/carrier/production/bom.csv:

Designator,Footprint,Quantity,Value,LCSC Part #
C1,0805,1,10uF,C15850
"C10, C3, C9",0402,3,1uF,C52923
"C11, C13, C16, C17, C2, C4, C8",0402,7,100nF,C1525
C12,0603,1,1uF,C15849
"C14, C15, C18, C19",0402,4,10uF,C15525
"C5, C6",0805,2,22uF,C45783
C7,0603,1,10uF,C19702
D1,SOT-23-6_L2.9-W1.6-P0.95-LS2.8-BL,1,USBLC6-2SC6_C2687116,C2687116
"J1, J4, J5, J6, J8",JST_SH_SM02B-SRSS-TB_1x02-1MP_P1.00mm_Horizontal,5,Conn_01x02,C160402
J2,JST_SH_SM08B-SRSS-TB_1x08-1MP_P1.00mm_Horizontal,1,Conn_01x08,C160407
J3,JST_SH_SM04B-SRSS-TB_1x04-1MP_P1.00mm_Horizontal,1,Conn_01x04,C160404
J7,USB_C_Receptacle_ShouHan_TYPE-C-16PLT-H6.5_Vertical,1,USB_C_Receptacle_USB2.0_16P,C3151748
L1,L_Murata_DFE201610P_NoSilk,1,2.2uH,C5832344
M1,Walter_Module_2x14_THT,1,Walter,Walter (DPTechnics)
Q1,SOT-363_SC-70-6,1,UMH3N,C62892
Q2,SOT-23-3_L2.9-W1.3-P1.90-LS2.4-BR,1,AO3400A,C20917
Q3,SOT-23-3_L2.9-W1.3-P1.90-LS2.4-BR,1,MMBT3904-C20526,C20526
Q4,SOT-23,1,AO3401A,C15127
"R1, R2, R3, R31, R32, R9",0402,6,100k,C25741
R10,0603,1,15R,C22810
"R11, R21, R23, R25, R27, R4, R5",0402,7,10k,C25744
"R12, R13, R14, R15, R26, R28",0402,6,4.7k,C25900
"R16, R17, R18",0402,3,220R,C25091
"R19, R29",0402,2,1M,C26083
"R20, R6, R7",0402,3,0R,C17168
R22,0402,1,18k,C25762
R24,0402,1,620R,C4961
"R30, R33",0402,2,51k,C25794
R8,0402,1,1k,C11702
SW1,SW-SMD_4P-L5.2-W5.2-P3.70-LS6.4,1,TS-1187A-S16,C42420254
SW2,SW_SPDT_ShouHan_MSS12C02LS_TopActuated,1,SW_SPDT,C3008584
U1,TQFN-16_L3.0-W3.0-P0.50-BL-EP1.7,1,CH343P,C2846043
U2,VSSOP-8_2.3x2mm_P0.5mm,1,74LVC2G126,C2652104
U3,TSSOP-10_3x3mm_P0.5mm,1,DRV2605LDGSR,C527464
U4,LGA-12_2x2mm_P0.5mm_NoSilk,1,LIS2DW12TR-MS,C50385411
U5,BQ25185_WSON-10_DLH0010A_2.2x2mm_P0.4mm_EP0.9x1.5mm,1,BQ25185DLHR,C19725033
U6,TDFN-8-1EP_2x2mm_P0.5mm_EP0.8x1.2mm,1,MAX17048G+T10,C2682616
U7,HVSSOP-8_L3.0-W3.0-P0.65-LS4.9-BL-EP,1,TPS62842DGRR,C2873354

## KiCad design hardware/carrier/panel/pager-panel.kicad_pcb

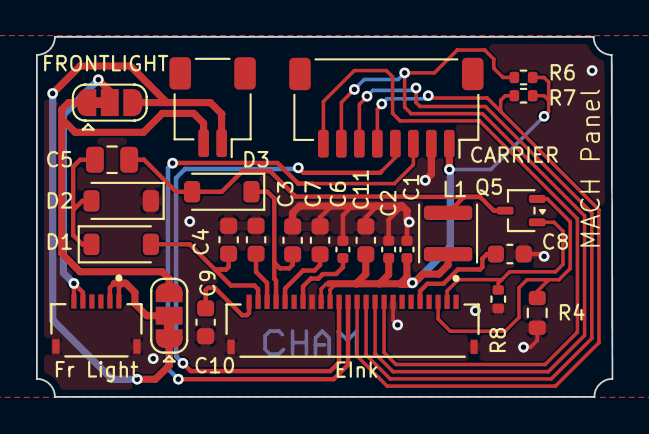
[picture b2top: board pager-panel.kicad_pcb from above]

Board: 2 copper layers, 32.0 x 20.0 mm, 27 parts (1 on the bottom side), 23 nets.

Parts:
C1: 10uF; C_0402_1005Metric
C2, C6: 1uF; C_0402_1005Metric
C3, C4, C7, C8, C9, C10: 1uF/25V; C_0603_1608Metric
C5: 4.7uF/25V; C_0805_2012Metric
C11: 4.7uF; C_0603_1608Metric
D1, D2, D3: B5819W; D_SOD-123
J1: EInk; HRS_FH34SRJ-24S-0.5SH_50_
J2: Fr Light; HRS_FH34SRJ-6S-0.5SH_50_
J3: CARRIER; JST_SH_SM08B-SRSS-TB_1x08-1MP_P1.00mm_Horizontal
J4: FRONTLIGHT; JST_SH_SM02B-SRSS-TB_1x02-1MP_P1.00mm_Horizontal
JP1, JP2: FL polarity; SolderJumper-3_P1.3mm_Bridged12_RoundedPad1.0x1.5mm
L1: 47uH; L_Sunlord_SWPA3015S
Q5: SI1308EDL; SOT-323_SC-70
R4: 2.2R; R_0603_1608Metric
R6, R7: 10k; R_0402_1005Metric
R8: 1M; R_0402_1005Metric
TP1: GND; TestPoint_Pad_D1.0mm

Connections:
3V3_EPD: C1.1, C2.1, C11.1, J1.15, J1.16, J3.1, L1.1, R6.1, R7.1
/EINK_BUSY: J1.9, J3.8
/EINK_CS: J1.12, J3.5, R7.2
/EINK_DC: J1.11, J3.6
/EINK_MOSI: J1.14, J3.4
/EINK_RST: J1.10, J3.7, R6.2
/EINK_SCK: J1.13, J3.3
/EPD_GDR: J1.2, Q5.1 (G), R8.1
/EPD_RESE: J1.3, Q5.2 (S), R4.1
/EPD_VCOM: C10.1, J1.24
/EPD_VDD: C6.1, J1.18
/EPD_VGH: C3.1, D3.1 (K), J1.21
/EPD_VGL: C4.1, D1.2 (A), J1.23
/EPD_VSH1: C7.1, J1.20
/EPD_VSH2: C8.1, J1.5
/EPD_VSL: C9.1, J1.22
EPD_SW: C5.1, D3.2 (A), L1.2, Q5.3 (D)
FL_A: J2.1, J2.2, JP1.2 (C)
FL_K: J2.5, J2.6, JP2.2 (C)
FL_N: J4.2, JP1.3 (B), JP2.1 (A)
FL_P: J4.1, JP1.1 (A), JP2.3 (B)
GND: C1.2, C2.2, C3.2, C4.2, C6.2, C7.2, C8.2, C9.2, C10.2, C11.2, D2.1 (K), J1.8, J1.17, J1.S1 (SHIELD), J1.S2 (SHIELD), J2.S1 (SHIELD), J2.S2 (SHIELD), J3.2, R4.2, R8.2, TP1.1
unnamed: C5.2, D1.1 (K), D2.2 (A)

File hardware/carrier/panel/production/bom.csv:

Designator,Footprint,Quantity,Value,LCSC Part #
C1,0402,1,10uF,C15525
"C10, C3, C4, C7, C8, C9",0603,6,1uF/25V,C15849
C11,0603,1,4.7uF,C19666
"C2, C6",0402,2,1uF,C52923
C5,0805,1,4.7uF/25V,C1779
"D1, D2, D3",D_SOD-123,3,B5819W,C8598
J1,HRS_FH34SRJ-24S-0.5SH_50_,1,EInk,C324726
J2,HRS_FH34SRJ-6S-0.5SH_50_,1,Fr Light,C224194
J3,JST_SH_SM08B-SRSS-TB_1x08-1MP_P1.00mm_Horizontal,1,CARRIER,C160407
J4,JST_SH_SM02B-SRSS-TB_1x02-1MP_P1.00mm_Horizontal,1,FRONTLIGHT,C160402
L1,L_Sunlord_SWPA3015S,1,47uH,C83435
Q5,SOT-323_SC-70,1,SI1308EDL,C469327
R4,0603,1,2.2R,C22939
"R6, R7",0402,2,10k,C25744
R8,0402,1,1M,C26083

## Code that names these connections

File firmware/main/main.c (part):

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    if (board_is_carrier()) {
        int vbus, s1, s2;
        board_read_charger_pins(&vbus, &s1, &s2);
        printf("IO%d VBUS_DET=%d  IO%d CHG_STAT1=%d  IO%d CHG_STAT2=%d\n", PAGER_PIN_VBUS_DET, vbus,
               PAGER_PIN_CHG_STAT1, s1, PAGER_PIN_CHG_STAT2, s2);
    }
    return 0;
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    } else {
        printf("fuel: gauge read failed\n");
    }
    printf("IO%d VBUS_DET=%d  IO%d CHG_STAT1=%d  IO%d CHG_STAT2=%d\n", PAGER_PIN_VBUS_DET, vbus,
           PAGER_PIN_CHG_STAT1, s1, PAGER_PIN_CHG_STAT2, s2);
    return ok ? 0 : 1;
}
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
